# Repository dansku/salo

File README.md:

# Salo Lamp

## Objectives 
* Develop a lamp connected to the internet where you can control it via a mobile application.
* Fully open source hardware/software
* Focus on low cost
* More to come...

## Dev Videos

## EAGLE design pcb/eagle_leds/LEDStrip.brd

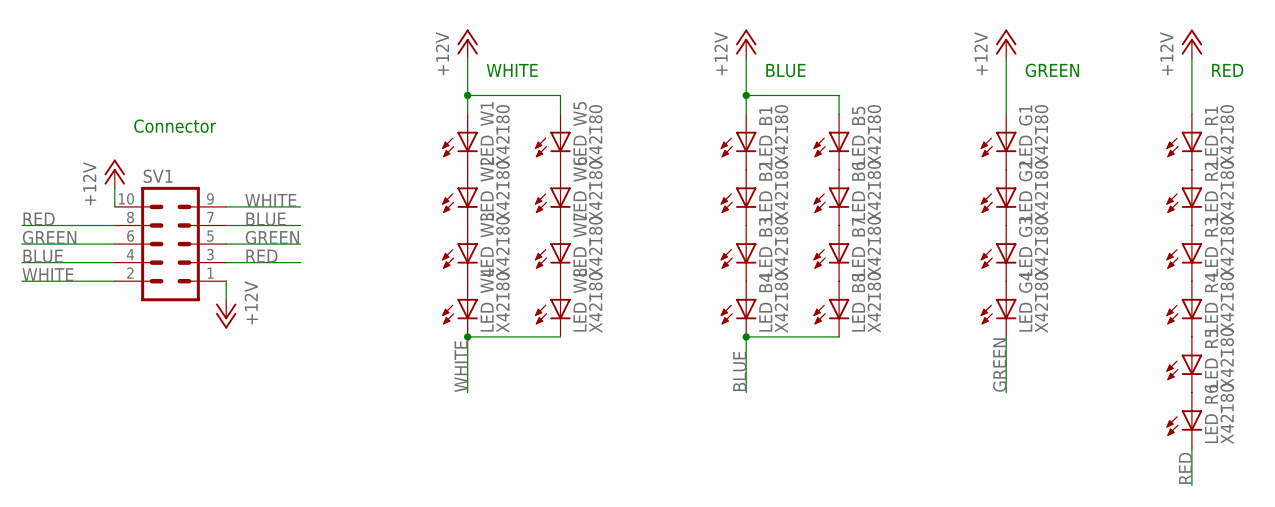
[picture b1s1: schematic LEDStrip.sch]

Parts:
LED_B1, LED_B2, LED_B3, LED_B4, LED_B5, LED_B6, LED_B7, LED_B8: X42180; Z-POWER-LED-DOME-TYPE
LED_G1, LED_G2, LED_G3, LED_G4: X42180; Z-POWER-LED-DOME-TYPE
LED_R1, LED_R2, LED_R3, LED_R4, LED_R5, LED_R6: X42180; Z-POWER-LED-DOME-TYPE
LED_W1, LED_W2, LED_W3, LED_W4, LED_W5, LED_W6, LED_W7, LED_W8: X42180; Z-POWER-LED-DOME-TYPE
SV1: MA05-2

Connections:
+12V: LED_B1.A, LED_B5.A, LED_G1.A, LED_R1.A, LED_W1.A, LED_W5.A, SV1.1, SV1.10
BLUE: LED_B4.C, LED_B8.C, SV1.4, SV1.7
GREEN: LED_G4.C, SV1.5, SV1.6
unnamed: LED_W1.C, LED_W2.A
unnamed: LED_W2.C, LED_W3.A
unnamed: LED_W3.C, LED_W4.A
unnamed: LED_W5.C, LED_W6.A
unnamed: LED_W6.C, LED_W7.A
unnamed: LED_W7.C, LED_W8.A
unnamed: LED_R4.C, LED_R5.A
unnamed: LED_B1.C, LED_B2.A
unnamed: LED_B2.C, LED_B3.A
unnamed: LED_B3.C, LED_B4.A
unnamed: LED_B5.C, LED_B6.A
unnamed: LED_B6.C, LED_B7.A
unnamed: LED_B7.C, LED_B8.A
unnamed: LED_G1.C, LED_G2.A
unnamed: LED_G2.C, LED_G3.A
unnamed: LED_G3.C, LED_G4.A
unnamed: LED_R1.C, LED_R2.A
unnamed: LED_R2.C, LED_R3.A
unnamed: LED_R3.C, LED_R4.A
unnamed: LED_R5.C, LED_R6.A
RED: LED_R6.C, SV1.3, SV1.8
WHITE: LED_W4.C, LED_W8.C, SV1.2, SV1.9

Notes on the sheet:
WHITE
BLUE
GREEN
RED
Connector

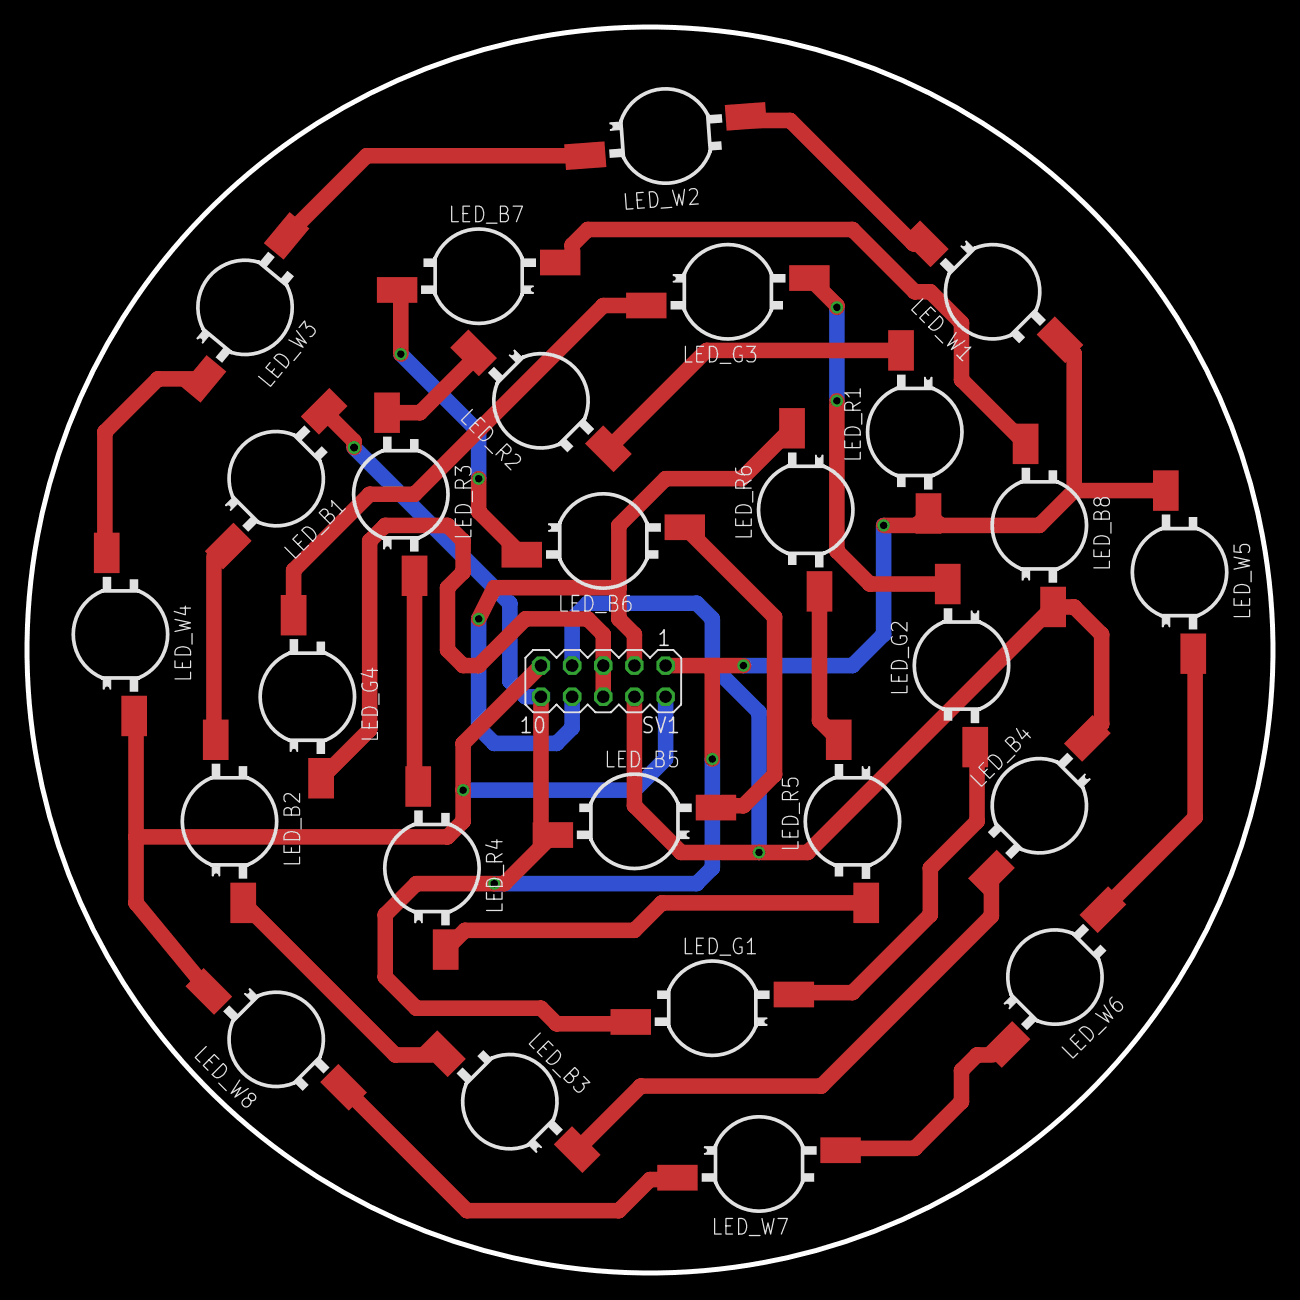
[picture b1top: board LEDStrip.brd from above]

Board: 2 copper layers, 101.6 x 101.6 mm, 27 parts (0 on the bottom side), 25 nets.

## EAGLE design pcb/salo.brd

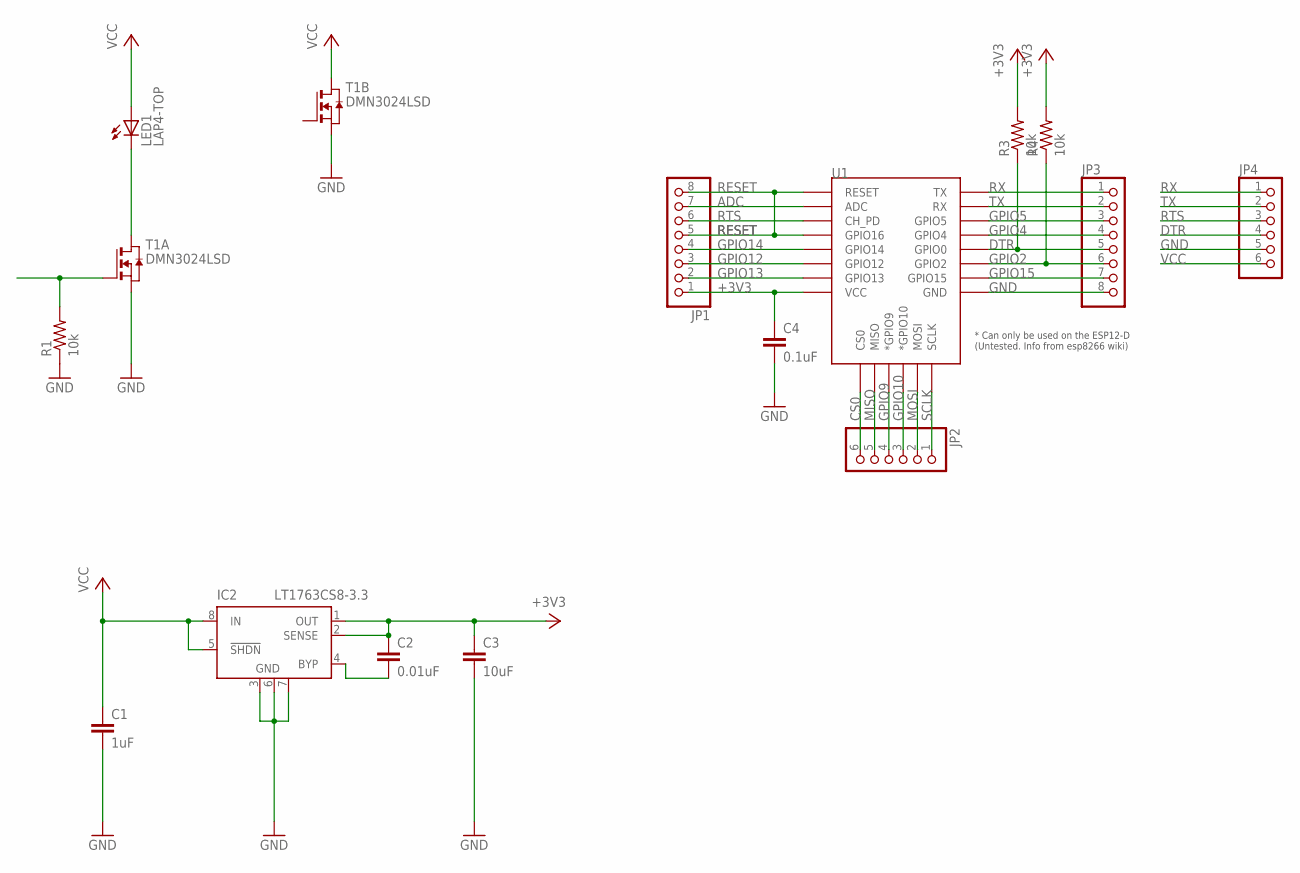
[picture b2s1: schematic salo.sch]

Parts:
C1: 1uF; C0805
C2: 0.01uF; C0805
C3: 10uF; C0805
C4: 0.1uF; C0805
IC2: LT1763CS8-3.3; SOIC8
JP1, JP3: PINHD-1X8; 1X08
JP2, JP4: PINHD-1X6; 1X06
LED1: LAP4-TOP; P47F-TOP
R1, R3, R4: 10k; R0805
T1: DMN3024LSD; SO8
U1: ESP12ESMD; ESP12E-SMD

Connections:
+3V3: C2.1, C3.1, C4.1, IC2.1 (OUT), IC2.2 (SENSE), JP1.1, R3.2, R4.2, U1.VCC
ADC: JP1.7, U1.ADC
BYPASS: C2.2, IC2.4 (BYP)
CS0: JP2.6, U1.CS0
DTR: JP3.5, JP4.4, R3.1, U1.GPIO0
GND: C1.2, C3.2, C4.2, IC2.3 (GND), IC2.6 (GND), IC2.7 (GND), JP3.8, JP4.5, R1.1, T1.1 (S), T1.3 (S), U1.GND
GPIO2: JP3.6, R4.1, U1.GPIO2
GPIO4: JP3.4, U1.GPIO4
GPIO5: JP3.3, U1.GPIO5
GPIO9: JP2.4, U1.GPIO9 (*GPIO9)
GPIO10: JP2.3, U1.GPIO10 (*GPIO10)
GPIO12: JP1.3, U1.GPIO12
GPIO13: JP1.2, U1.GPIO13
GPIO14: JP1.4, U1.GPIO14
GPIO15: JP3.7, U1.GPIO15
MISO: JP2.5, U1.MISO
MOSI: JP2.2, U1.MOSI
unnamed: R1.2, T1.2 (G)
unnamed: LED1.C, T1.7 (D), T1.8 (D)
RESET: JP1.5, JP1.8, U1.GPIO16, U1.RESET
RTS: JP1.6, JP4.3, U1.CH_PD
RX: JP3.1, JP4.1, U1.TXD0 (TX)
SCLK: JP2.1, U1.SCLK
TX: JP3.2, JP4.2, U1.RXD0 (RX)
VCC: C1.1, IC2.5 (!SHDN), IC2.8 (IN), JP4.6, LED1.A, T1.5 (D), T1.6 (D)

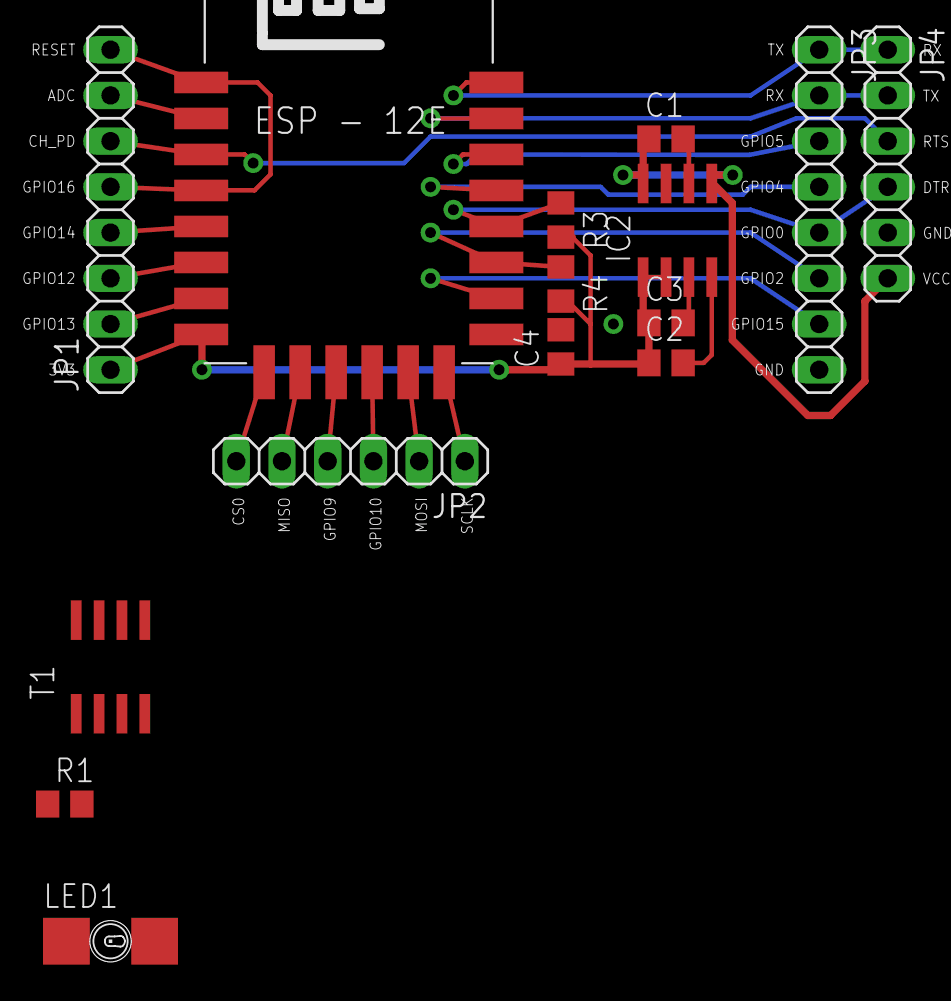
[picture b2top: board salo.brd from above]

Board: 2 copper layers, 15 parts (0 on the bottom side), 25 nets.

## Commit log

2016-05-18 Initial test code.
2016-05-18 Started objectives.
2016-05-19 initial experimentation with VR
2016-05-21 working version of lifx control
2016-05-22 Add LED research/idea
2016-05-22 Fix bottom row
2016-05-22 Move A.
2016-05-22 implemented color spectrum and highlight
2016-05-22 Add Eagle starting files.
2016-05-22 Add transistor research
2016-05-23 Add 2x N-channel enhancement MOSFET, SO-8.
2016-05-23 Mode dev to Platformio.
2016-05-23 Change wifi name for configuration
2016-05-23 Building system and serial communication working.
2016-05-23 Add fadeToColor function. May be inverted for now.
2016-05-23 Fix fadeToColor order.
2016-05-24 Choose if you want fadeToColor or not. Change most integers from int to uint8.
2016-05-24 Shorten if statement
2016-05-24 Code refactoring.
2016-05-24 Changed Serial.print to printf.
2016-05-24 Simplfies variable arrays.
2016-06-01 Create test bed pcb.
2016-06-22 Add test leds pcb
2016-07-02 Update with led count
2016-07-02 Add demo video
2016-07-02 Update img size
2016-07-05 Update pin numbers as red was bliking on boot.
2016-07-25 Update files.
2016-07-25 Add gitignore
2016-08-17 Add OSRAM info
2016-08-17 Update red voltage
2016-08-18 Removed old components
2016-08-18 Add led driver
2016-08-18 Add Led Driver resistors

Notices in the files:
parts and their libraries:
SparkFun-Aesthetics: Licensing: Creative Commons ShareAlike 4.0 International - https://creativecommons.org/licenses/by-sa/4.0
